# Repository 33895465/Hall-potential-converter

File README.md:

# Hall-potential-converter
### 用於將霍爾電位器的訊號轉換成類比可變電阻訊號的轉換器，也可以使用RS485進行通訊
### Converter for converting Hall potentiometer signal into analog variable resistance signal, and can communicate by RS485 

* Components list:
  *  Arduino pro mini
  *  MX485
  *  X9C105

* PCB EDA software: Autodesk eagle

Accelrator_PCB原理圖

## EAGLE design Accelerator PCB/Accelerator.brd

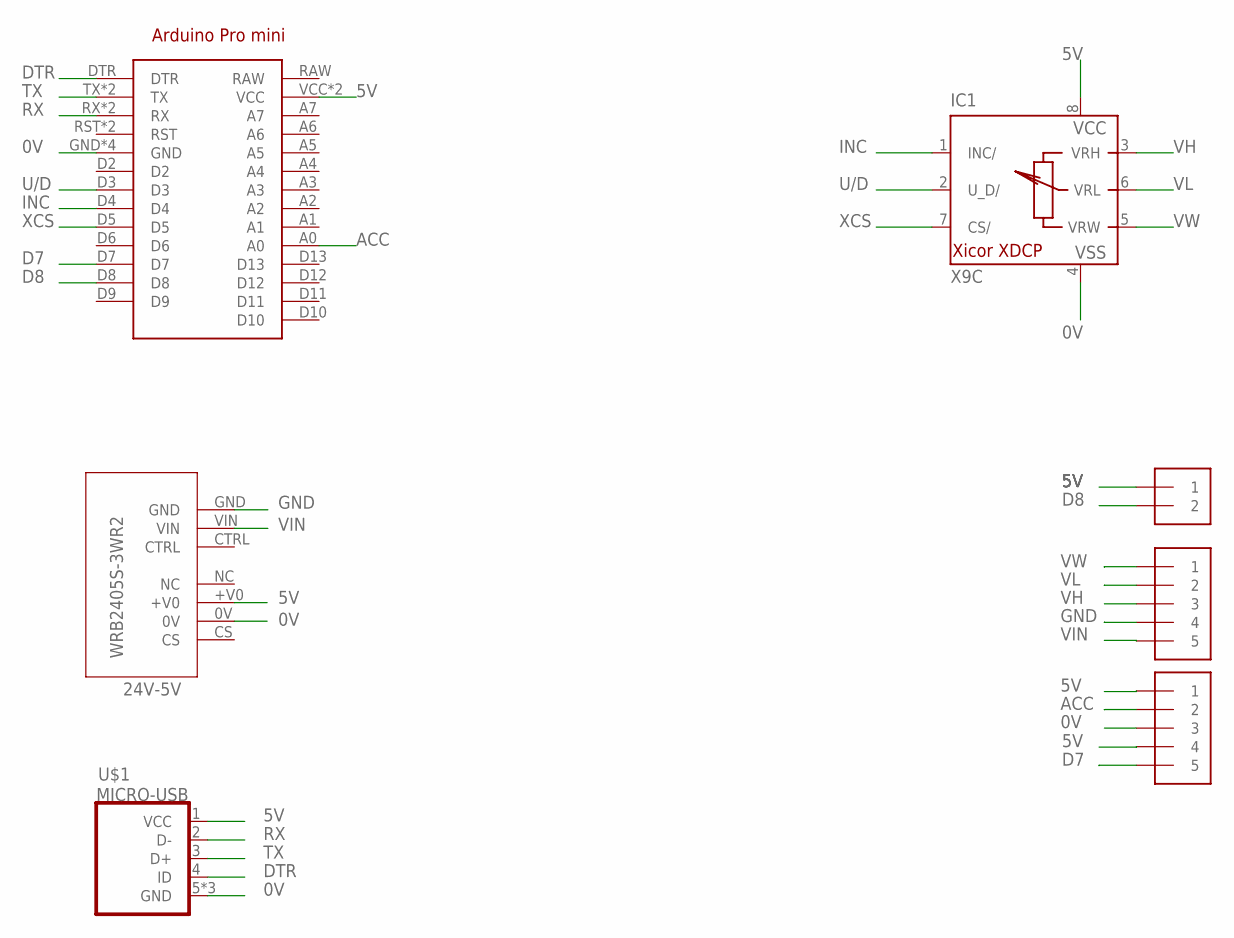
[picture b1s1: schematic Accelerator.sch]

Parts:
ARDUINO1: ARDUINO_PRO_MINI
IC1: X9C; DIL08
J1, J2: 1X5; 1X05-3.5MM
J3: 1X2-3.5MM
U2: WRB2405S-3WR2
U$1: MICRO-USB

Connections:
0V: ARDUINO1.GND, ARDUINO1.GND@1 (GND), ARDUINO1.GND@2 (GND), ARDUINO1.GND@3 (GND), IC1.4 (VSS), J2.3, U2.0V, U$1.5 (GND), U$1.GND1 (GND), U$1.GND2 (GND)
5V: ARDUINO1.VCC, ARDUINO1.VCC@1 (VCC), IC1.8 (VCC), J2.1, J2.4, J3.1, U2.+V0, U$1.1 (VCC)
ACC: ARDUINO1.A0, J2.2
D7: ARDUINO1.D7, J2.5
D8: ARDUINO1.D8, J3.2
DTR: ARDUINO1.DTR, U$1.4 (ID)
GND: J1.4, U2.GND
INC: ARDUINO1.D4, IC1.1 (INC/)
RX: ARDUINO1.RX, ARDUINO1.RX@1 (RX), U$1.2 (D-)
TX: ARDUINO1.TX, ARDUINO1.TX@1 (TX), U$1.3 (D+)
U/D: ARDUINO1.D3, IC1.2 (U_D/)
VH: IC1.3 (VRH), J1.3
VIN: J1.5, U2.VIN
VL: IC1.6 (VRL), J1.2
VW: IC1.5 (VRW), J1.1
XCS: ARDUINO1.D5, IC1.7 (CS/)

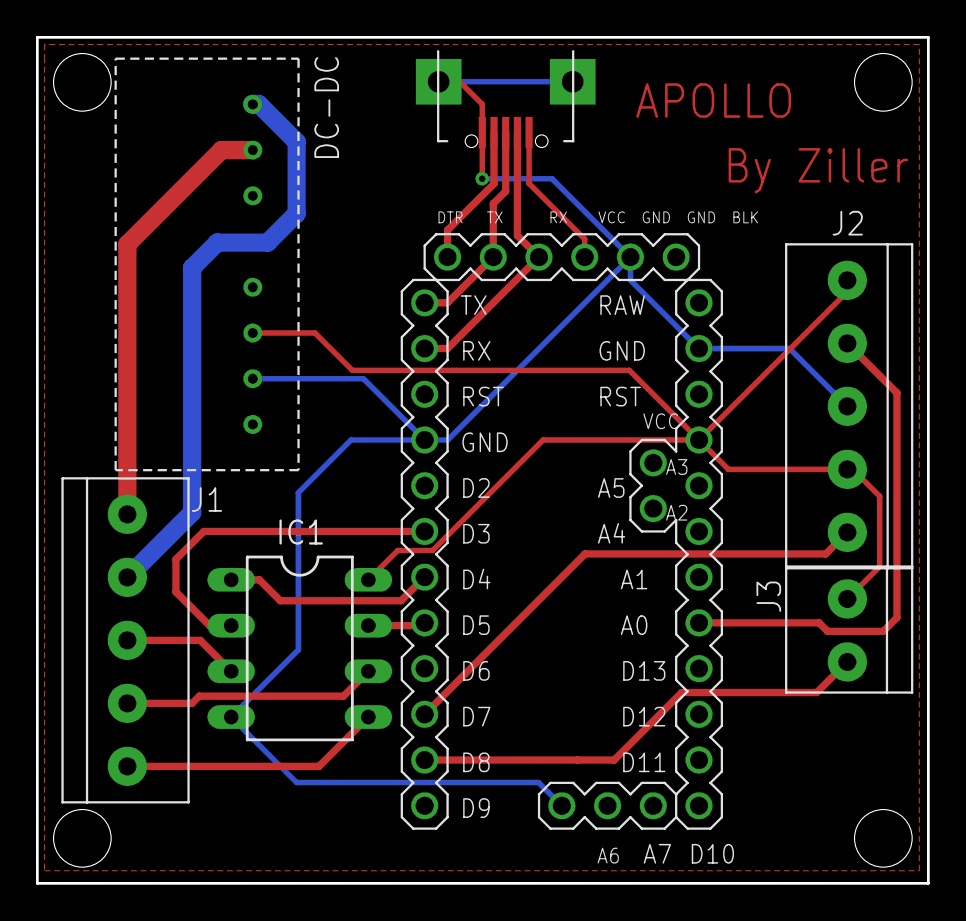
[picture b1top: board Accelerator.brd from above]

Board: 2 copper layers, 49.5 x 47.0 mm, 7 parts (0 on the bottom side), 16 nets.

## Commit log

2023-04-12 ADD the converter PCB layout file
2023-04-12 Add the converter code
